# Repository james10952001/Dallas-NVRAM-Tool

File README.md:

The original intent of this project was to enable bytewise editing of the memory 
and RTC registers of Dallas timekeeping RAM parts used in a lot of older test equipment
such as the DS1644 and DS1742 used in the Tektronix TDS300 and TDS3000 series oscilloscopes.
In the process of implementing that I realized it was trivial to allow reading virtually any
parallel memory device of 32 pins or less and writing to any SRAM or NVRAM so I added support
for other devices I had on hand. 
While it is usually possible to dump the contents of Dallas devices with a TL866 or similar
device programmer, attempting to write to one will stomp on the RTC and status bytes which
can result in the chip's test mode being enabled or other issues. With this you can view and
manipulate individual bytes such as the power on hours of the TDS3000, view and set the 
time/date/day, and activate the test mode while measuring the frequency. I have tried to make
it relatively simple to add support for additional parts and I will try to do so as examples
come into my possession.

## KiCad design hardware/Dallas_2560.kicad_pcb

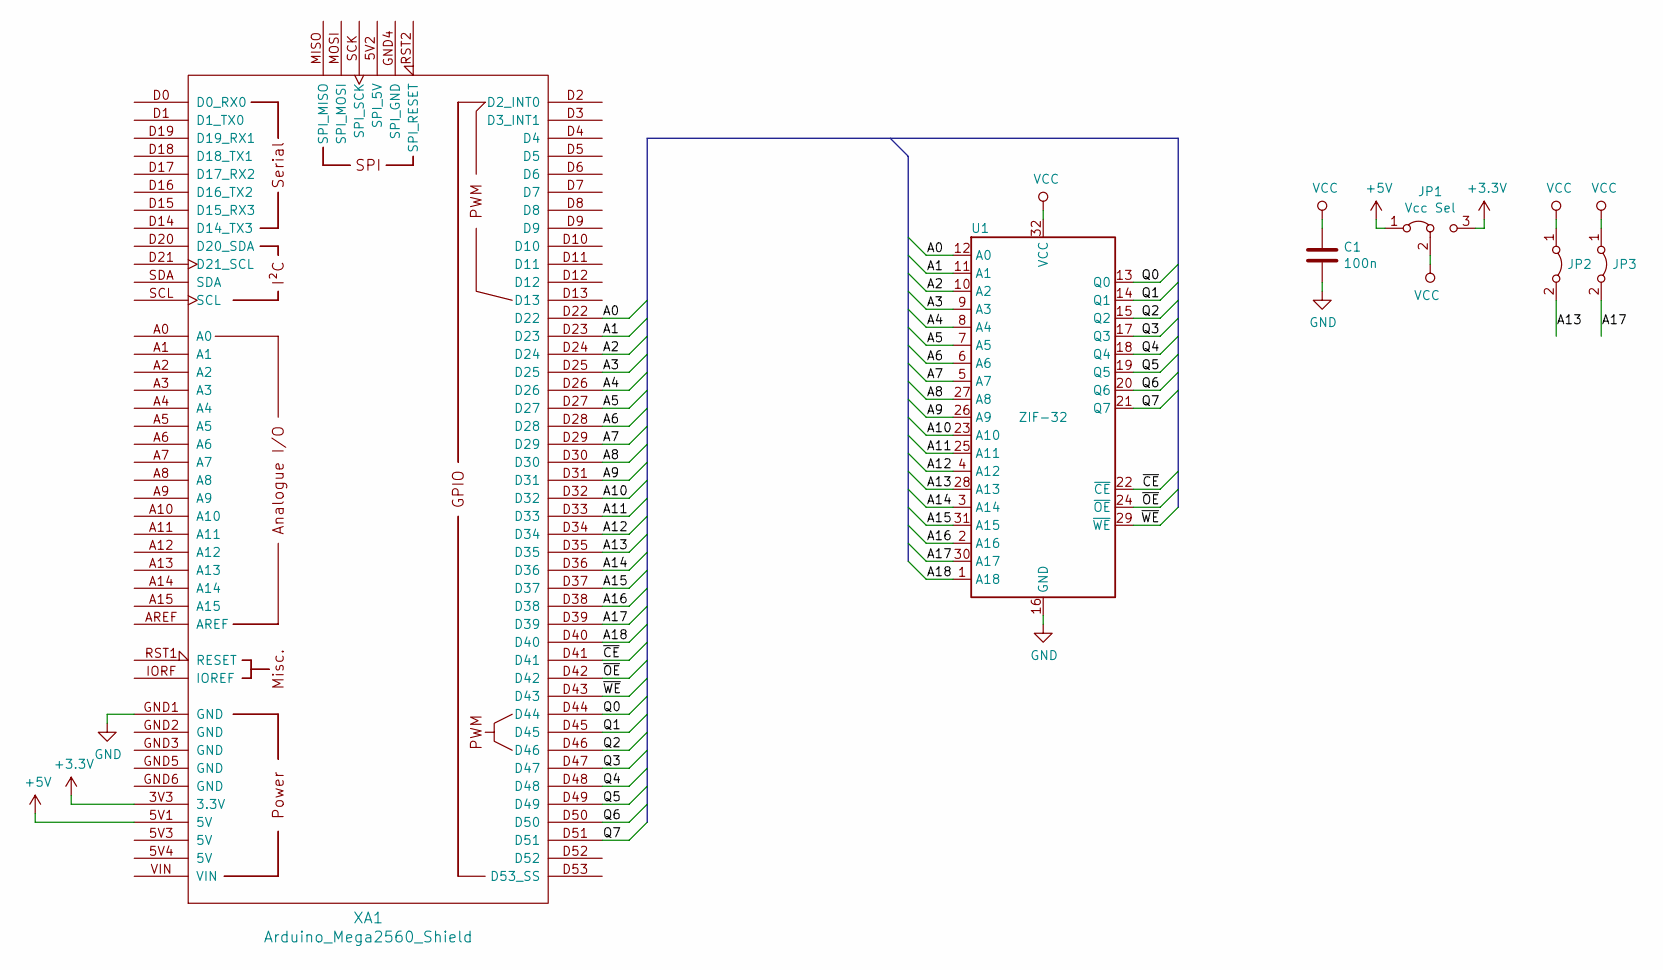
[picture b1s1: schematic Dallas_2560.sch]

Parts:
C1: 100n; C_0805_2012Metric
JP1: Vcc Sel; PinHeader_1x03_P2.54mm_Vertical
JP2, JP3: JP; PinHeader_1x02_P2.54mm_Vertical
U1: ZIF-32; DIP_Socket-32_W11.9_W12.7_W15.24_W17.78_W18.5_3M_232-1285-0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
XA1: Arduino_Mega2560_Shield

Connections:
+3V3: JP1.3 (B), XA1.3V3 (3.3V)
+5V: JP1.1 (A), XA1.5V1 (5V)
/A0: U1.12 (A0), XA1.D22
/A1: U1.11 (A1), XA1.D23
/A2: U1.10 (A2), XA1.D24
/A3: U1.9 (A3), XA1.D25
/A4: U1.8 (A4), XA1.D26
/A5: U1.7 (A5), XA1.D27
/A6: U1.6 (A6), XA1.D28
/A7: U1.5 (A7), XA1.D29
/A8: U1.27 (A8), XA1.D30
/A9: U1.26 (A9), XA1.D31
/A10: U1.23 (A10), XA1.D32
/A11: U1.25 (A11), XA1.D33
/A12: U1.4 (A12), XA1.D34
/A13: JP2.2 (B), U1.28 (A13), XA1.D35
/A14: U1.3 (A14), XA1.D36
/A15: U1.31 (A15), XA1.D37
/A16: U1.2 (A16), XA1.D38
/A17: JP3.2 (B), U1.30 (A17), XA1.D39
/A18: U1.1 (A18), XA1.D40
/Q0: U1.13 (Q0), XA1.D44
/Q1: U1.14 (Q1), XA1.D45
/Q2: U1.15 (Q2), XA1.D46
/Q3: U1.17 (Q3), XA1.D47
/Q4: U1.18 (Q4), XA1.D48
/Q5: U1.19 (Q5), XA1.D49
/Q6: U1.20 (Q6), XA1.D50
/Q7: U1.21 (Q7), XA1.D51
/~CE: U1.22 (~CE), XA1.D41
/~OE: U1.24 (~OE), XA1.D42
/~WE: U1.29 (~WE), XA1.D43
GND: C1.2, U1.16 (GND), XA1.GND1 (GND)
VCC: C1.1, JP1.2 (C), JP2.1 (A), JP3.1 (A), U1.32 (VCC)

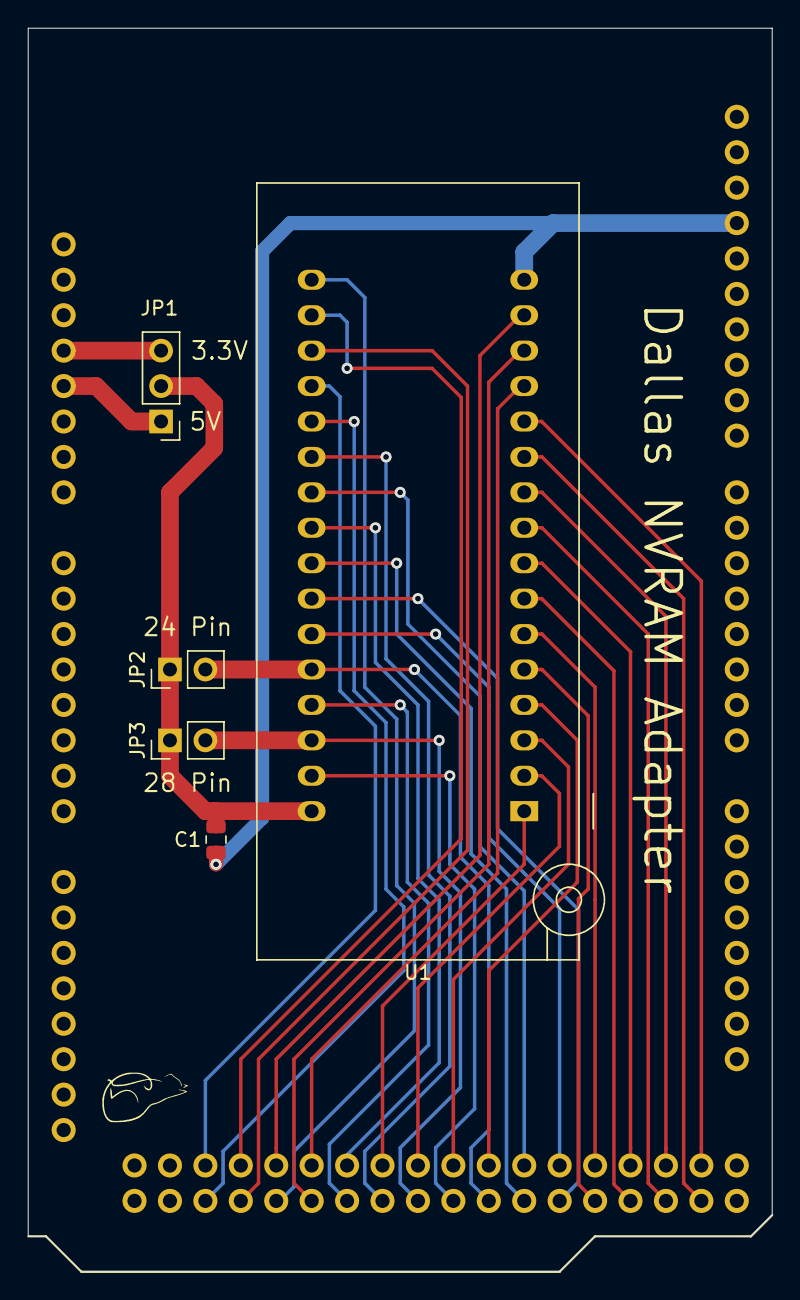
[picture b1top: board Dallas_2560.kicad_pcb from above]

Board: 2 copper layers, 53.3 x 89.2 mm, 7 parts (0 on the bottom side), 34 nets.

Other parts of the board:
VAL: REF; cat_300

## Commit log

2026-05-28 Rename Dallas_2550.kicad_prl to hardware/Dallas_2550.kicad_prl
2026-05-28 Rename Dallas_2560-cache.lib to hardware/Dallas_2560-cache.lib
2026-05-28 Rename Dallas_2560.bak to hardware/Dallas_2560.bak
2026-05-28 Rename Dallas_2560.kicad_pcb to hardware/Dallas_2560.kicad_pcb
2026-05-28 Rename Dallas_2560.kicad_pcb-bak to hardware/Dallas_2560.kicad_pcb-bak
2026-05-28 Rename Dallas_2560.kicad_prl to hardware/Dallas_2560.kicad_prl
2026-05-28 Rename Dallas_2560.kicad_pro to hardware/Dallas_2560.kicad_pro
2026-05-28 Rename Dallas_2560.kicad_sch to hardware/Dallas_2560.kicad_sch
2026-05-28 Rename Dallas_2560.net to hardware/Dallas_2560.net
2026-05-28 Rename Dallas_2560.pro to hardware/Dallas_2560.pro
2026-05-28 Rename Dallas_2560.sch to hardware/Dallas_2560.sch
2026-05-28 Rename fp-info-cache to hardware/fp-info-cache
2026-05-28 Rename fp-lib-table to hardware/fp-lib-table
2026-05-28 Rename sym-lib-table to hardware/sym-lib-table
2026-05-28 Rename memtoolv1.ino to firmware/memtoolv1.ino
    Initial release of the firmware.
